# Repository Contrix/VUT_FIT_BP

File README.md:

# Bakalářská práce
### Vestavěný systém pro monitorování výšky vodní hladiny

Autor práce: Jiří Hanák\
Ak. rok: 2018/2019\
Vedoucí: Ing. Václav Šimek\
Oponent: Ing. Tomáš Kašpárek\
Publikace na webu školy: https://www.vutbr.cz/studenti/zav-prace/detail/122051

##### Abstrakt 
Tato práce se zabývá návrhem a realizací vestavěného systému pro monitorování výšky vodní hladiny. Účelem systému je řízení napouštění nádrže na základě výšky vodní hladiny. V první řadě je věnována pozornost přehledu stávajících měřicích technik a výběru vhodných měřicích prvků pro daný scénář. Vestavěný systém staví na bezkontaktních snímačích TFmini a JSN-SR04T-2.0. Řízení systému obstarává mikrokontrolér řady STM32F0 od firmy STMicroelectronics programovaný v jazyce C s využitím abstraktní vrstvy HAL. Naměřené výsledky jsou odesílány přes Wi-Fi SoC ESP8266EX na demonstrační server v jazyce Python.

##### Klíčová slova
Vestavěný systém, měření vzdálenosti, STM32, návrh DPS, nádrž, voda, ESP8266, ČSN EN 60 529, HAL

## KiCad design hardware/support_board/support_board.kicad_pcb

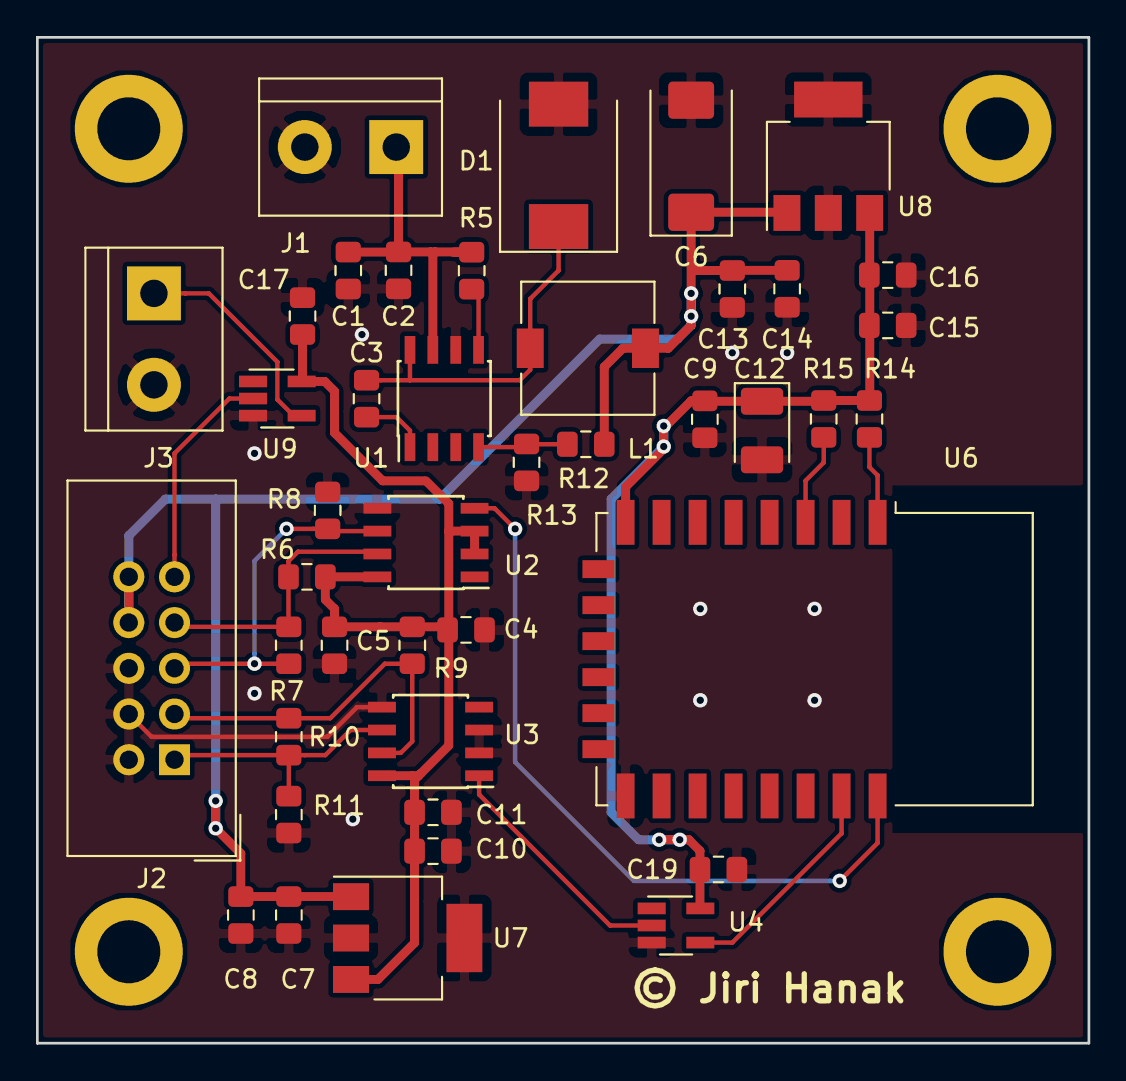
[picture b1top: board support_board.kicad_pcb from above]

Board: 2 copper layers, 58.4 x 55.9 mm, 46 parts (0 on the bottom side), 20 nets.

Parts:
C1, C2, C8, C14: 4.7u; C_0805_2012Metric_Pad1.15x1.40mm_HandSolder
C3: 10n; C_0805_2012Metric_Pad1.15x1.40mm_HandSolder
C4, C5, C7, C9, C11, C13, C16, C17, C19: 100n; C_0805_2012Metric_Pad1.15x1.40mm_HandSolder
C6: 100u/10V; CP_EIA-7343-31_Kemet-D
C10, C15: 1u; C_0805_2012Metric_Pad1.15x1.40mm_HandSolder
C12: 22u/10V; CP_EIA-3528-21_Kemet-B_Pad1.50x2.35mm_HandSolder
D1: B340; D_SMC
J1: IN_12V; TerminalBlock_bornier-2_P5.08mm
J2: Main_board; IDC-Header_2x05_P2.54mm_Vertical
J3: SSR_control; TerminalBlock_bornier-2_P5.08mm
L1: 22uH; L_7.3x7.3_H4.5
N1, N2, N3, N4: Screw
R5, R14, R15: 10k; R_0805_2012Metric_Pad1.15x1.40mm_HandSolder
R6, R8, R9, R11: 1k; R_0805_2012Metric_Pad1.15x1.40mm_HandSolder
R7, R10: 150R; R_0805_2012Metric_Pad1.15x1.40mm_HandSolder
R12: 330k; R_0805_2012Metric_Pad1.15x1.40mm_HandSolder
R13: 56k; R_0805_2012Metric_Pad1.15x1.40mm_HandSolder
U1: TPS5420D; SOIC-8_3.9x4.9mm_P1.27mm
U2, U3: SN75LBC176D; SOIC-8_3.9x4.9mm_P1.27mm
U4, U9: SN74LV1T34; SOT-23-5_HandSoldering
U6: ESP-12E
U7: MCP1826S_5V; SOT-223-3_TabPin2
U8: MCP1826S_3.3V; SOT-223-3_TabPin2

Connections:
+3V3: C9.1, C12.1, C15.1, C16.1, C19.2, R14.1, R15.1, U4.5, U6.8, U8.3
+5.5V: C6.1, C7.1, C8.1, C13.1, C14.1, J2.8, J2.10, L1.2, R12.1, U7.1, U8.1
+5V: C4.2, C5.2, C10.1, C11.1, C17.2, R6.1, R9.1, U2.2, U2.3, U2.8, U3.8, U7.3, U9.5
/12V: C1.1, C2.1, J1.1, R5.2, U1.7
GND: C1.2, C2.2, C4.1, C5.1, C6.2, C7.2, C8.2, C9.2, C10.2, C11.2, C12.2, C13.2, C14.2, C15.2, C16.2, C17.1, C19.1, D1.2, J1.2, J2.2, J2.4, J2.6, J3.2, R8.2, R11.2, R13.2, U1.6, U2.5, U3.2, U3.3, U3.5, U4.3, U6.15, U7.2, U8.2, U9.3
unnamed: C3.1, D1.1, L1.1, U1.8
unnamed: C3.2, U1.1
unnamed: J2.1, R10.2, R11.1, U3.6
unnamed: J2.3, R9.2, R10.1, U3.7
unnamed: J2.5, R7.2, R8.1, U2.6
unnamed: J2.7, R6.2, R7.1, U2.7
unnamed: J2.9, U9.2
unnamed: J3.1, U9.4
unnamed: R5.1, U1.5
unnamed: R12.2, R13.1, U1.4
unnamed: R14.2, U6.1
unnamed: R15.2, U6.3
unnamed: U2.4, U6.22
unnamed: U3.1, U4.2
unnamed: U4.4, U6.21

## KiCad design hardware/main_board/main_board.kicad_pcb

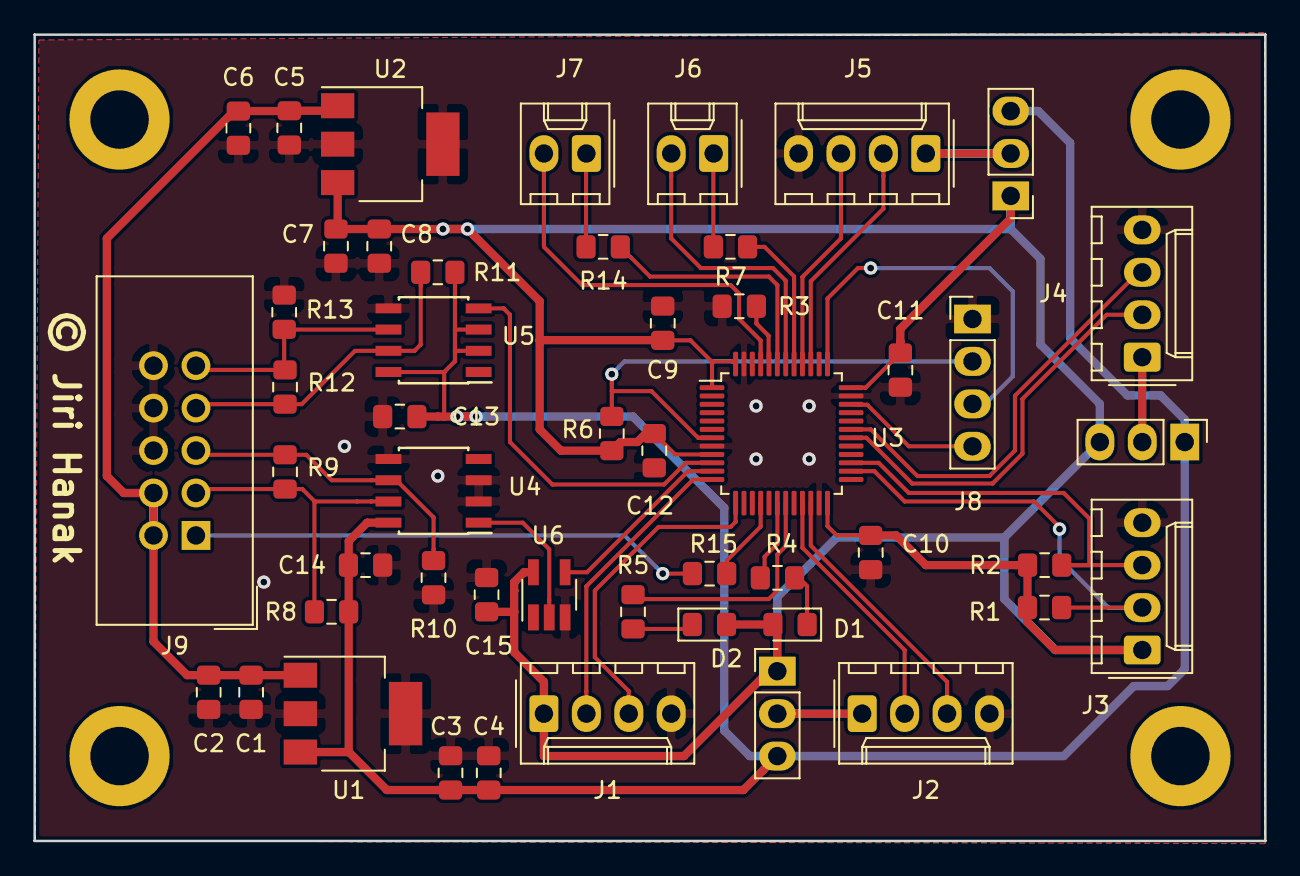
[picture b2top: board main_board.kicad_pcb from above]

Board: 2 copper layers, 73.7 x 48.3 mm, 54 parts (0 on the bottom side), 40 nets.

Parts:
C1, C4, C5, C8, C9, C10, C11, C12, C13, C14, C15: 100n; C_0805_2012Metric_Pad1.15x1.40mm_HandSolder
C2, C6: 4.7u; C_0805_2012Metric_Pad1.15x1.40mm_HandSolder
C3, C7: 1u; C_0805_2012Metric_Pad1.15x1.40mm_HandSolder
D1, D2: LED; LED_0805_2012Metric_Pad1.15x1.40mm_HandSolder
J1: UART2; Molex_KK-254_AE-6410-04A_1x04_P2.54mm_Vertical
J2: UART3; Molex_KK-254_AE-6410-04A_1x04_P2.54mm_Vertical
J3: I2C; Molex_KK-254_AE-6410-04A_1x04_P2.54mm_Vertical
J4: UART1; Molex_KK-254_AE-6410-04A_1x04_P2.54mm_Vertical
J5: UART5; Molex_KK-254_AE-6410-04A_1x04_P2.54mm_Vertical
J6: BTN_X; Molex_KK-254_AE-6410-02A_1x02_P2.54mm_Vertical
J7: BTN_Y; Molex_KK-254_AE-6410-02A_1x02_P2.54mm_Vertical
J8: prg_conn; PinHeader_1x04_P2.54mm_Vertical
J9: Support_board; IDC-Header_2x05_P2.54mm_Vertical
N1, N2, N3, N4: Screw
R1, R2: 4k7; R_0805_2012Metric_Pad1.15x1.40mm_HandSolder
R3, R6: 10k; R_0805_2012Metric_Pad1.15x1.40mm_HandSolder
R4, R5, R7, R14, R15: 330R; R_0805_2012Metric_Pad1.15x1.40mm_HandSolder
R8, R10, R11, R13: 1k; R_0805_2012Metric_Pad1.15x1.40mm_HandSolder
R9, R12: 150R; R_0805_2012Metric_Pad1.15x1.40mm_HandSolder
SW1: SW_UART3; PinHeader_1x03_P2.54mm_Vertical
SW2: SW_UART5; PinHeader_1x03_P2.54mm_Vertical
SW5: SW_UART1; PinHeader_1x03_P2.54mm_Vertical
U1: MCP1826S_5V; SOT-223-3_TabPin2
U2: MCP1826S_3.3V; SOT-223-3_TabPin2
U3: STM32F030CCTx; LQFP-48_7x7mm_P0.5mm
U4, U5: SN75LBC176D; SOIC-8_3.9x4.9mm_P1.27mm
U6: SN74LV1T34; SOT-23-5_HandSoldering

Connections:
+3V3: C7.1, C8.1, C9.1, C10.1, C11.1, C12.1, C15.2, D1.2, D2.2, J1.1, J3.1, R1.1, R2.1, R6.1, SW1.1, SW2.1, SW5.3, U2.3, U3.1, U3.9, U3.24, U3.36, U3.48, U6.5
+5.5V: C1.1, C2.1, C5.1, C6.1, J9.2, J9.4, U1.1, U2.1
+5V: C3.1, C4.1, C13.1, C14.1, R8.1, R11.1, SW1.3, SW2.3, SW5.1, U1.3, U4.8, U5.2, U5.3, U5.8
/SCL: J3.2, R1.2, U3.26
/SDA: J3.3, R2.2, U3.27
/SDCLK: J8.3, U3.37
/SDWIO: J8.4, U3.34
/SSR_CONTROL: R15.1, U3.16
/UART1_RX: J4.3, U3.31
/UART1_TX: J4.2, U3.30
/UART2_RX: J1.3, U3.13
/UART2_TX: J1.2, U3.12
/UART3_RX: J2.3, U3.22
/UART3_TX: J2.2, U3.21
/UART4_RX: U3.11, U6.4
/UART4_TX: U3.10, U5.4
/UART5_RX: J5.3, U3.40
/UART5_TX: J5.2, U3.39
/~RST: J8.2, R6.2, U3.7
GND: C1.2, C2.2, C3.2, C4.2, C5.2, C6.2, C7.2, C8.2, C9.2, C10.2, C11.2, C12.2, C13.2, C14.2, C15.1, J1.4, J2.4, J3.4, J4.4, J5.4, J8.1, J9.6, J9.8, J9.10, R3.2, R10.2, R13.2, U1.2, U2.2, U3.8, U3.23, U3.35, U3.47, U4.2, U4.3, U4.5, U5.5, U6.3
unnamed: D1.1, R4.2
unnamed: D2.1, R5.1
unnamed: J2.1, SW1.2
unnamed: J5.1, SW2.2
unnamed: J4.1, SW5.2
unnamed: J6.1, R7.2
unnamed: J6.2, U3.42
unnamed: J9.1, R15.2
unnamed: J9.3, R8.2, R9.1, U4.7
unnamed: J9.5, R9.2, R10.1, U4.6
unnamed: J9.7, R11.2, R12.1, U5.7
unnamed: J9.9, R12.2, R13.1, U5.6
unnamed: J7.1, R14.2
unnamed: J7.2, U3.45
unnamed: R3.1, U3.44
unnamed: R4.1, U3.18
unnamed: R5.2, U3.19
unnamed: R7.1, U3.41
unnamed: R14.1, U3.43
unnamed: U4.1, U6.2

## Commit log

2019-10-24 Kopie odevzdanych souboru
2019-10-24 Doplneni dokumentace
2019-10-24 revize 1

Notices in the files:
hardware/main_board/main_board.kicad_pcb:
© Jiri Hanak
